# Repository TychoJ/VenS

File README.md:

# VenS
Voor versterkers en sensoren

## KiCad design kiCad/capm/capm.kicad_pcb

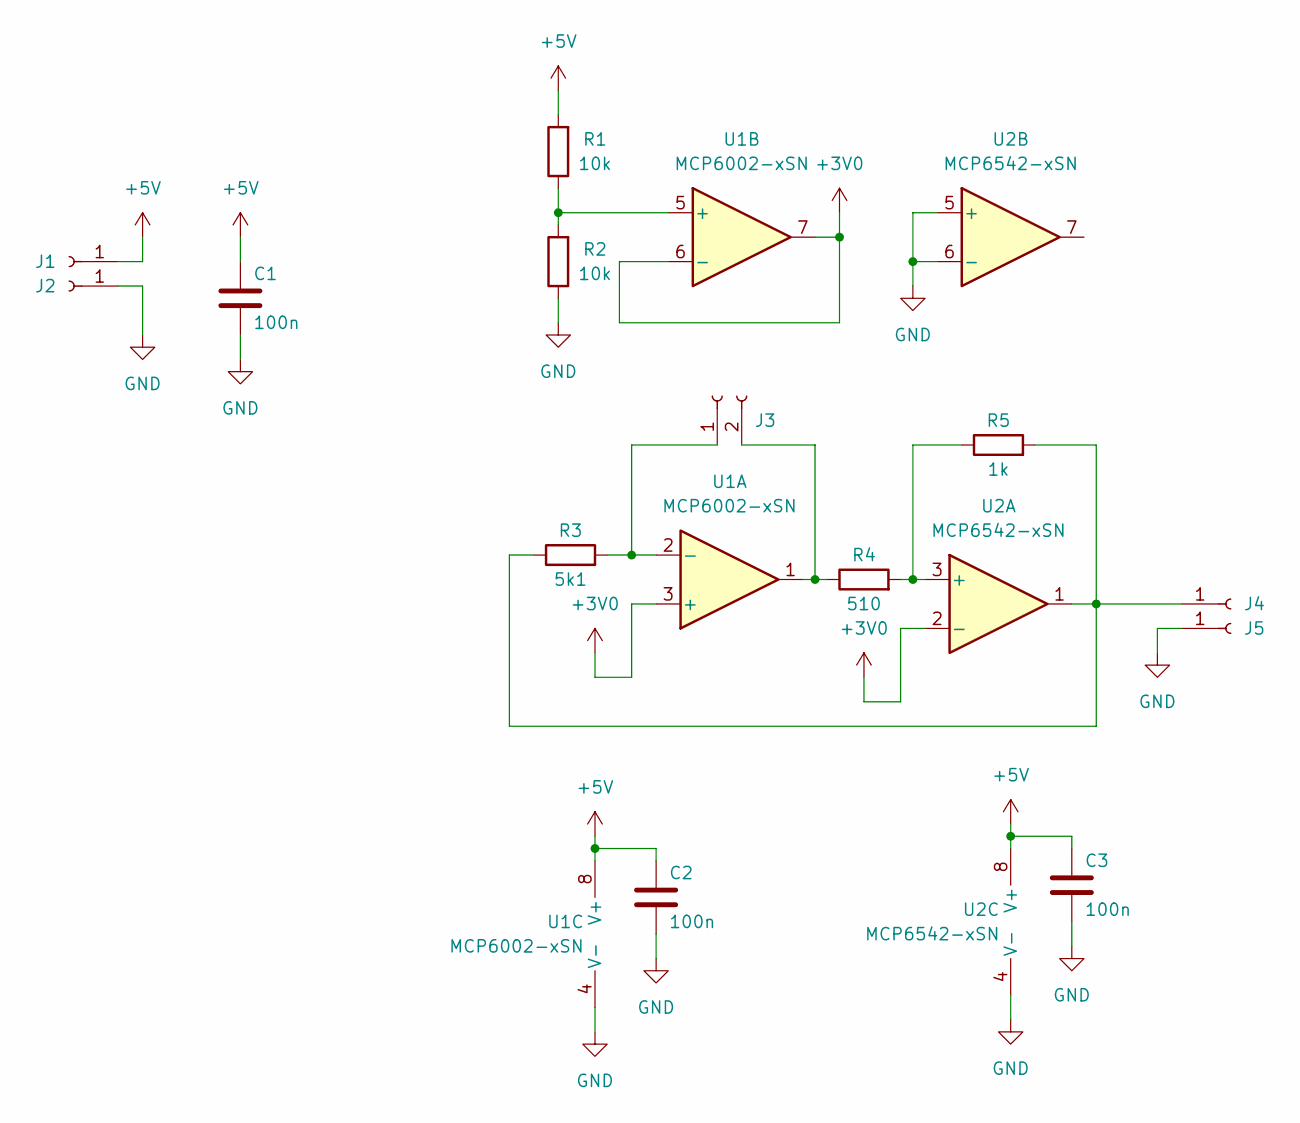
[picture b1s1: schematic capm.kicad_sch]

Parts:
C1, C2, C3: 100n; C_0805_2012Metric_Pad1.18x1.45mm_HandSolder
J1, J2, J4, J5: Conn_01x01_Female; PinHeader_1x01_P2.54mm_Vertical
J3: Conn_01x02_Female; HARWIN D2899
R1, R2: 10k; R_0805_2012Metric_Pad1.20x1.40mm_HandSolder
R3: 5k1; R_0805_2012Metric_Pad1.20x1.40mm_HandSolder
R4: 510; R_0805_2012Metric_Pad1.20x1.40mm_HandSolder
R5: 1k; R_0805_2012Metric_Pad1.20x1.40mm_HandSolder
U1: MCP6002-xSN; SO-8_3.9x4.9mm_P1.27mm
U2: MCP6542-xSN; SO-8_3.9x4.9mm_P1.27mm

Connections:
+3V0: U1.3 (+), U1.6 (-), U1.7, U2.2 (-)
+5V: C1.1, C2.1, C3.1, J1.1, R1.2, U1.8 (V+), U2.8 (V+)
GND: C1.2, C2.2, C3.2, J2.1, J5.1, R2.1, U1.4 (V-), U2.4 (V-), U2.5 (+), U2.6 (-)
unnamed: J3.1, R3.2, U1.2 (-)
unnamed: J3.2, R4.1, U1.1
unnamed: J4.1, R3.1, R5.2, U2.1
unnamed: R1.1, R2.2, U1.5 (+)
unnamed: R4.2, R5.1, U2.3 (+)

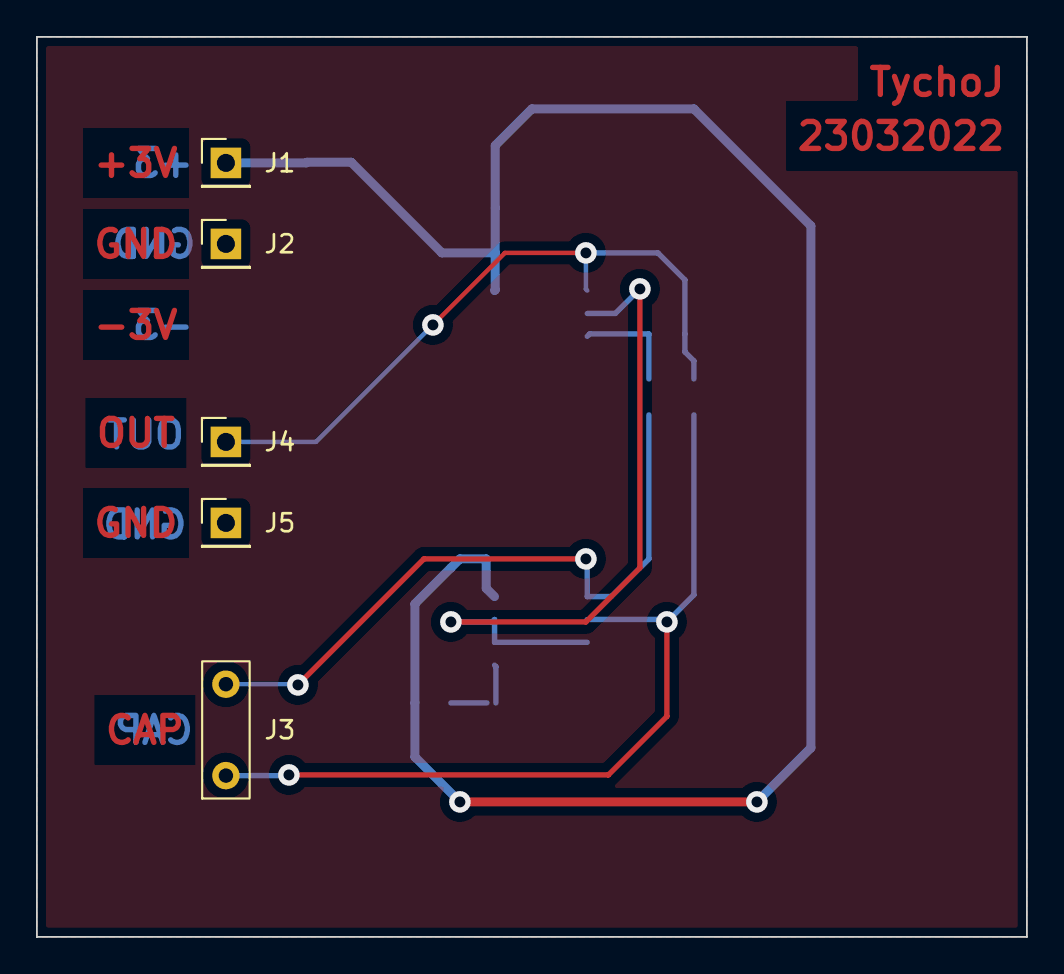
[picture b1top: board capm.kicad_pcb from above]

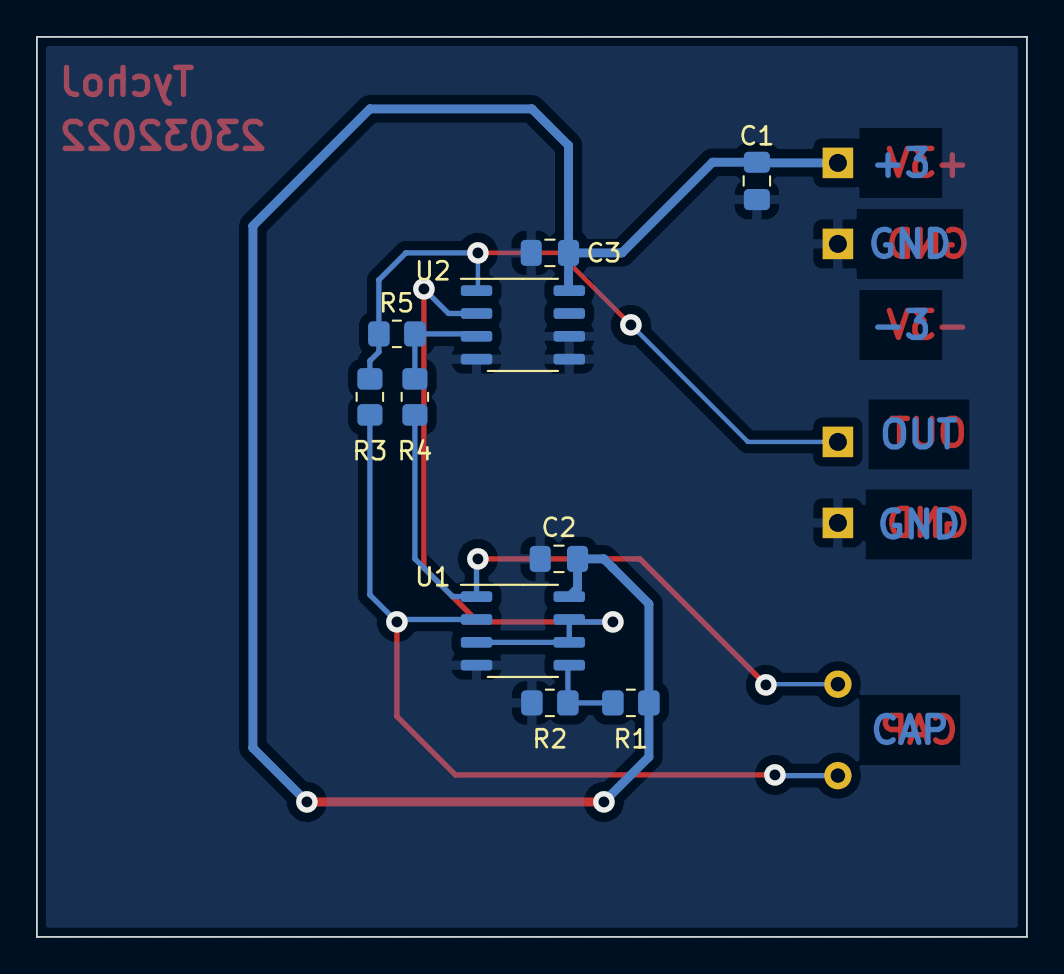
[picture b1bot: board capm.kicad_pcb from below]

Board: 2 copper layers, 55.0 x 50.0 mm, 15 parts (10 on the bottom side), 8 nets.

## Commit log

2022-03-02 fixed latex gitignore
2022-03-09 added Opdracht 2.7
2022-03-23 ltspice schakeling lol
2022-03-25 added kiCad files
2022-03-29 pcb update
2022-03-29 added interactive html bom
2022-03-29 formules
2022-03-29 formula.tex verbetert
2022-03-30 updated text in copper
